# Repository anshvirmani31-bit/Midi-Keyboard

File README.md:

# Midi-Keyboard
This is my week three project for half-life. The design and parts are different from the tutorial and I also made my own footprint for the capacitive touch pads.

# What is it?

As the name suggests, this is a midi keyboard. It essentially sends data to a computer which then transforms those signals into music. This can be used to create melodies when you don't have instruments on hand. It's also very convenient and easy to carry around since the PCB itself is less than 100x100mm. Another reason you may want to make this is because (I'm assuming) it's also fun to just play around with and see what kind of music you can make!

# How is mine different?

My midi keyboard is different than that of the tutorial because my footprint for the capacitive touch pads is different, as well as the layout. I also don't use any sliders because that exceeded the tier 1 budget (mainly due to shipping costs in my area). I also use 9 capacitive touchpads and 2 computer switches as opposed to 7 touchpads and 3 switches. My firmware is also different.

## How is my firmware different?

My firmware uses the template that was given in the tutorial however it is adjusted to my unique project. It accounts for 9 unique capacitive touch pads, two keyboard switches, and no sliders. This makes it my own unique code, not just copying and pasting the code that was given to us. I want to note that I watched youtube videos to learn how to change my code however I also used the google AI overview a little because there were some specific things that I couldn't find tutorials for made by real people online. My firmware is based on KMK as suggested to do in the tutorial.

# Images

## Finished KiCad PCB (3d view and normal)

### Normal view

### 3d view

#### Front

#### Back

# BOM

|Item                    |Qty|Supplier  |Cost/item|Total Cost|link                                                                                                                                                                                                                                                                                                                                                                                                                                                                                                  |
|------------------------|---|----------|---------|----------|------------------------------------------------------------------------------------------------------------------------------------------------------------------------------------------------------------------------------------------------------------------------------------------------------------------------------------------------------------------------------------------------------------------------------------------------------------------------------------------------------------------------------------------------------------------------------|
|ESP32-S3-ZERO           |1  |AliExpress|$1.81    |$1.81     |https://www.aliexpress.com/item/1005006642715384.html?                                                                                                                                                                                                                                                                                                                                                                                                                                                                                                                        |
|SK6812 MINI_E           |3  |AliExpress|$4.83    |$14.49    |https://www.aliexpress.com/item/1005007863635868.html?                                                                                                                                                                                                                                                                                                                                                                                                                                                                                                                        |
|360 Rotary Encoder      |1  |AliExpress|$2.78    |$2.78     |https://www.aliexpress.com/item/1005007644083514.html?                                                                                                                                                                                                                                                                                                                                                                                                                                                                                                                        |
|Keycaps                 |1  |Amazon    |$1.99    |$1.99     |https://www.amazon.ca/Dye-Subbed-Engraved-Cherry-MX-Mechanical-Cheryy-mx/dp/B0H1M5VVJJ/ref=sr_1_8?crid=31IBWCTARCE3J&dib=eyJ2IjoiMSJ9.3X9RbTJFJmBqfdfAQ1o6SrylQ5LzeQZUHT9f5bB5Vtrtik_js_f6pRRAZ7E8RfF6Pay9h43SubvgaOmxXVnrkj94xZ9x_g1OU49Hjs_OLbDrZEMkO3NDg3UltTatgSiNmjJHTo0eHEYp_u9OCF83F94n886aKqrdNLoplHu8O2Bo3hfFzxwhnufXSA7WZo4PFJ8hGxgKzcVP2PuN_qvE-KKRzUGv7K8SUN9kF38IKRc_r7YuckHQf4V-ec8AtfrSSxQ5HJh1XTK8jn2ZpBo0dbFnfWfdCwKo8BCB5xH33Q8.yUrJWX8nSMT1G7GCBi0HAb9_bSu6bN1ZfSxA-8C2EXI&dib_tag=se&keywords=cherry+mx+keycaps&qid=1792626652&sprefix=%2Caps%2C171&sr=8-8|
|PCB                     |1  |JLCPCB    |$4.00    |$4.00     |https://jlcpcb.com/                                                                                                                                                                                                                                                                                                                                                                                                                                                                                                                                                           |
|Estimated total shipping|1  |          |         |$4.91     |                                                                                                                                                                                                                                                                                                                                                                                                                                                                                                                                                                              |

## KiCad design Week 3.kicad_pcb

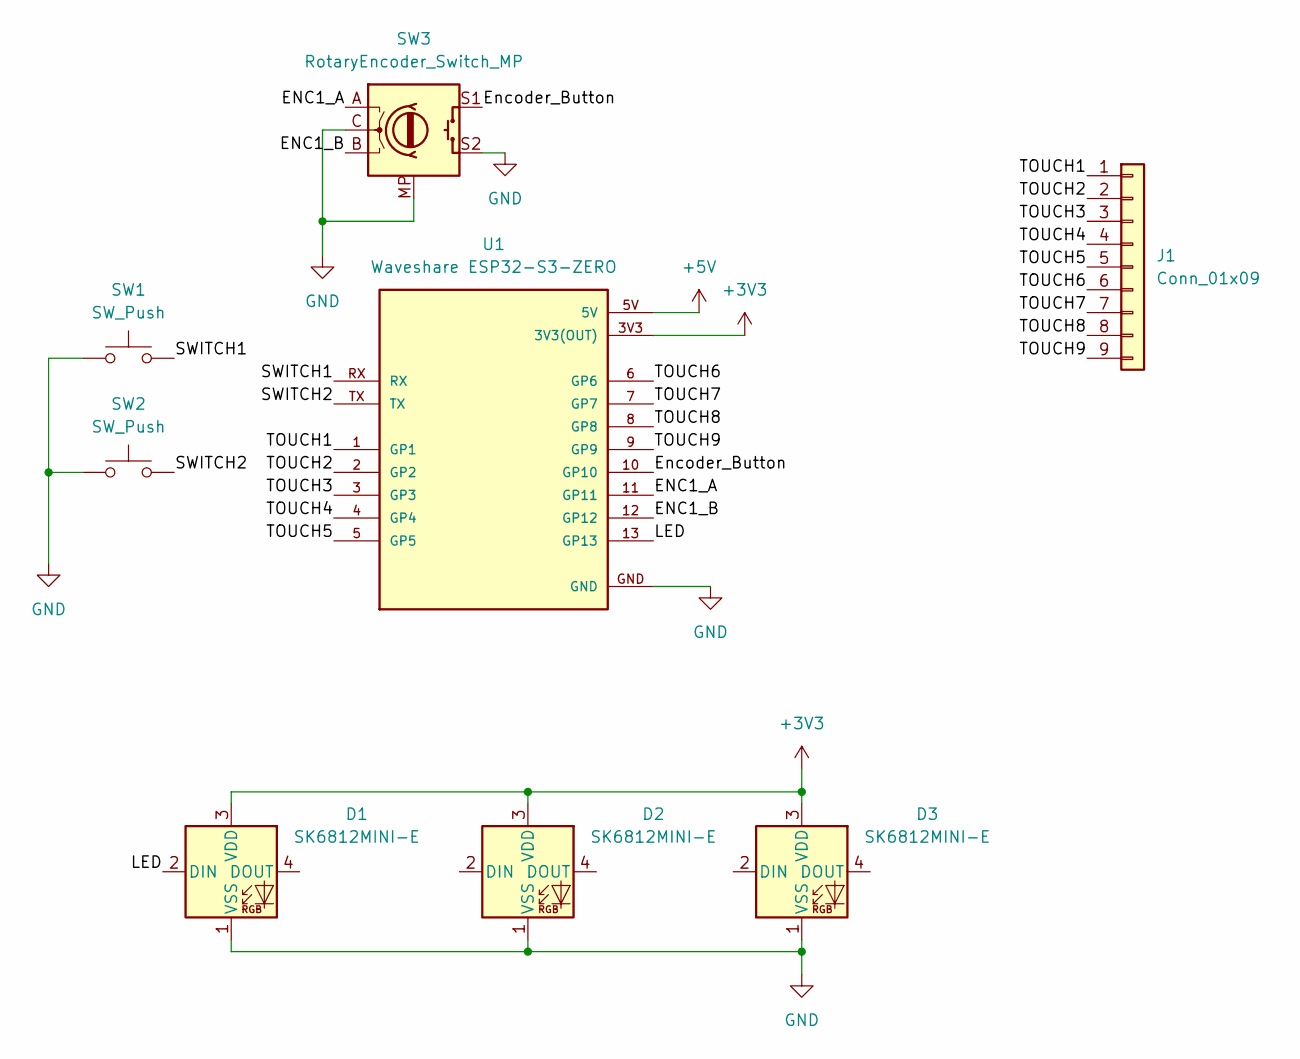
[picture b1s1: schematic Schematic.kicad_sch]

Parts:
D1, D2, D3: SK6812MINI-E; LED_SK6812MINI-E_3.2x2.8mm_P1.5mm_ReverseMount
J1: Conn_01x09; Capacitive Keys
SW1, SW2: SW_Push; SW_Cherry_MX_1.00u_PCB
SW3: RotaryEncoder_Switch_MP; RotaryEncoder_Alps_EC11E-Switch_Vertical_H20mm
U1: Waveshare ESP32-S3-ZERO; Waveshare ESP32-S3-Zero; PARTREV NA

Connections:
+3V3: D1.3 (VDD), D2.3 (VDD), D3.3 (VDD), U1.3V3 (3V3(OUT))
+5V: U1.5V
/ENC1_A: SW3.A, U1.11 (GP11)
/ENC1_B: SW3.B, U1.12 (GP12)
/Encoder_Button: SW3.S1, U1.10 (GP10)
/LED: D1.2 (DIN), U1.13 (GP13)
/SWITCH1: SW1.2, U1.RX
/SWITCH2: SW2.2, U1.TX
/TOUCH1: J1.1, U1.1 (GP1)
/TOUCH2: J1.2, U1.2 (GP2)
/TOUCH3: J1.3, U1.3 (GP3)
/TOUCH4: J1.4, U1.4 (GP4)
/TOUCH5: J1.5, U1.5 (GP5)
/TOUCH6: J1.6, U1.6 (GP6)
/TOUCH7: J1.7, U1.7 (GP7)
/TOUCH8: J1.8, U1.8 (GP8)
/TOUCH9: J1.9, U1.9 (GP9)
GND: D1.1 (VSS), D2.1 (VSS), D3.1 (VSS), SW1.1, SW2.1, SW3.C, SW3.MP, SW3.S2, U1.GND

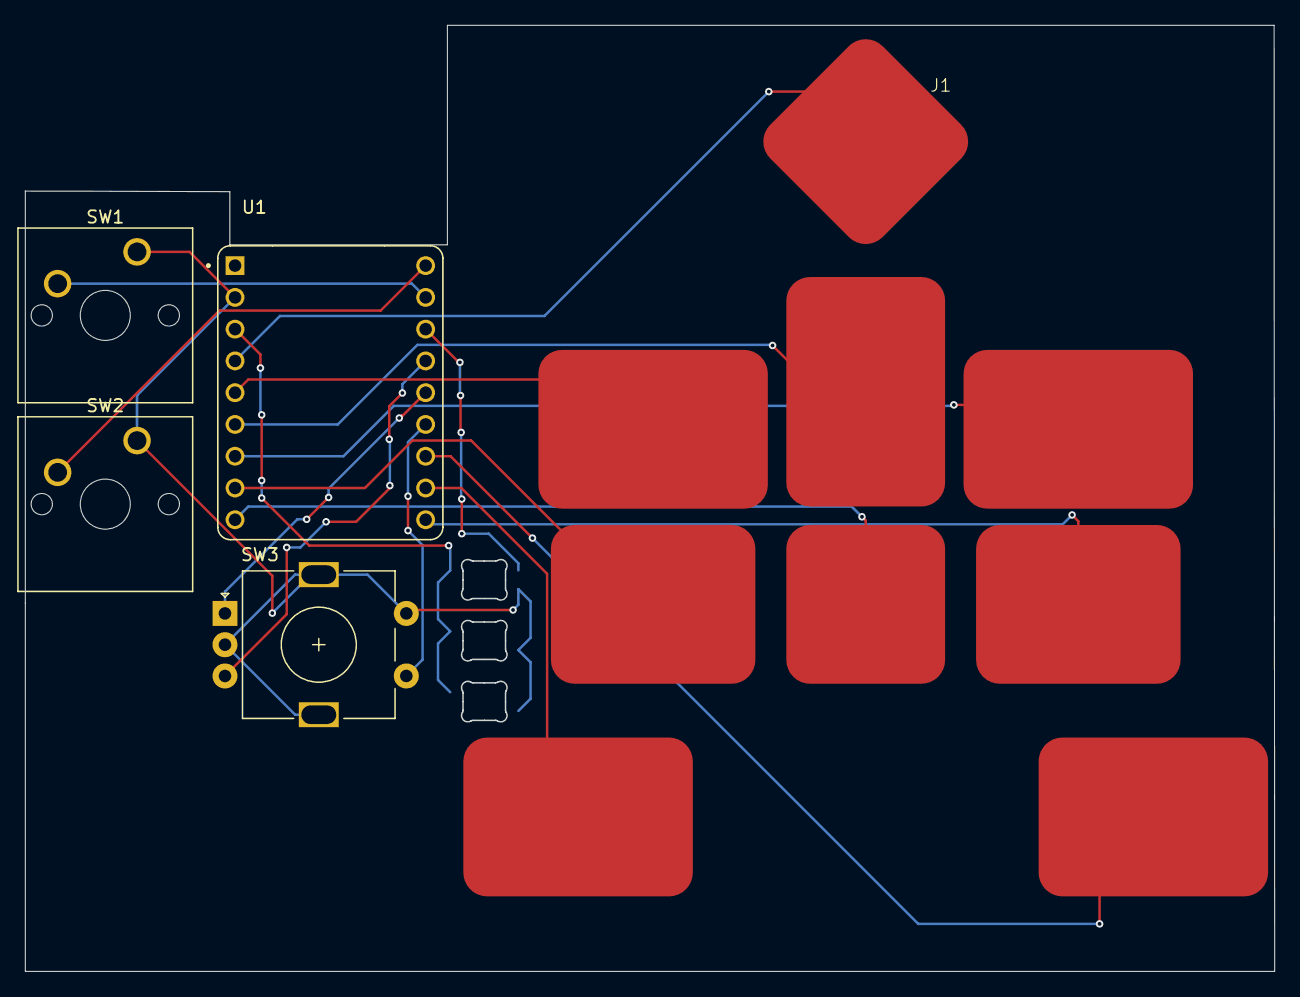
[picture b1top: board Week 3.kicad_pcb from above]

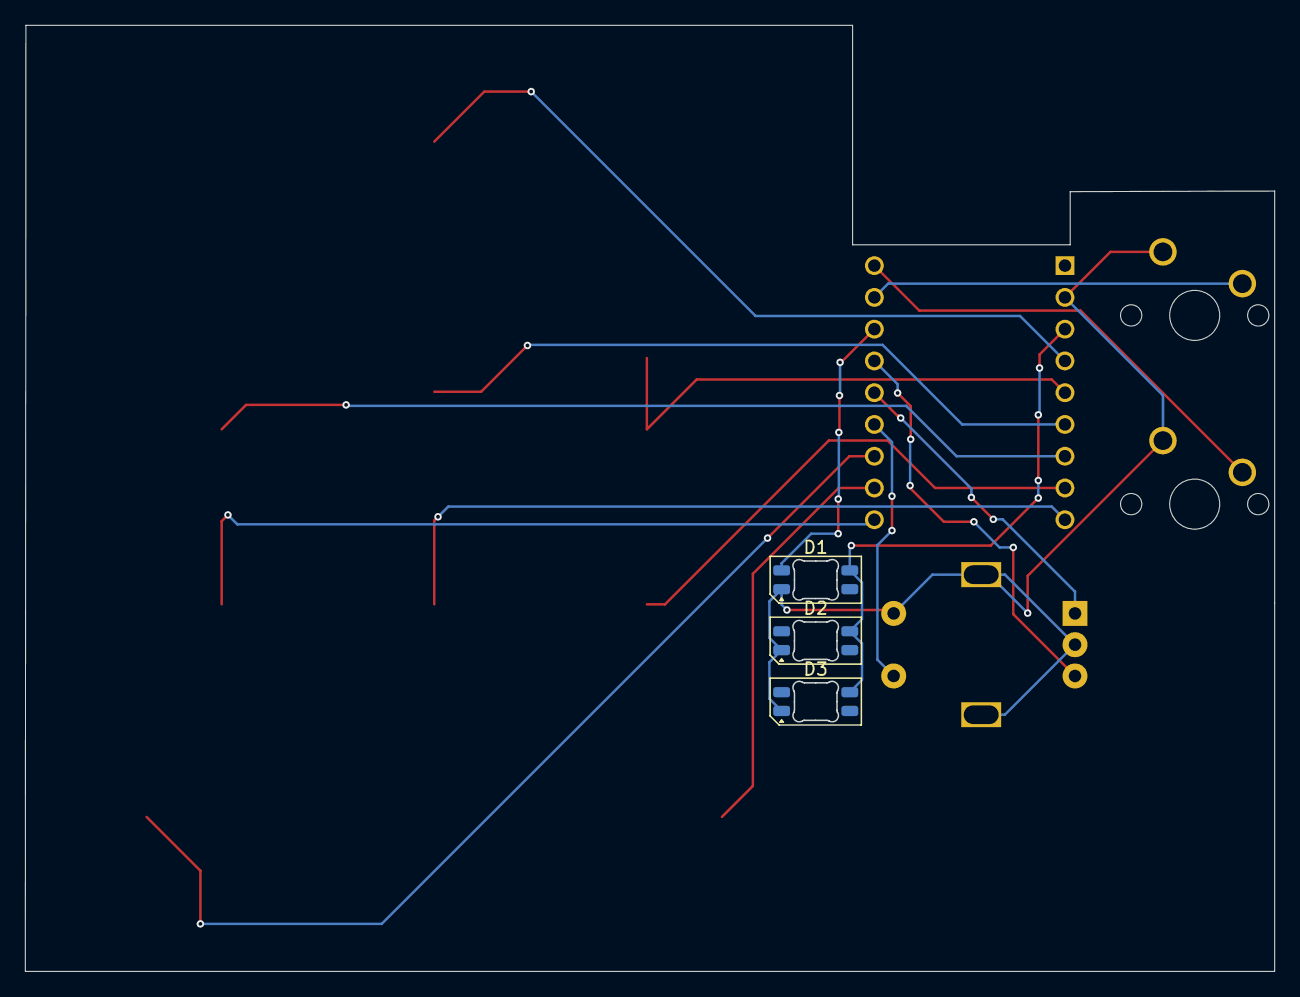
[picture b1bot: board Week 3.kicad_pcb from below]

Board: 2 copper layers, 99.9 x 75.6 mm, 8 parts (3 on the bottom side), 17 nets.
